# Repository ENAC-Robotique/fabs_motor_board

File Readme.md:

# Motor control board

STM32F767 based motor control board.

- control up to 3 DC motors
- 4 hardware encoder inputs.

**Holonomic drive:** Use the 3 motors, and the first 3 encoders.

**Differential drive:** Use the first 2 motors. Use the first 2 encodeurs for the motor encodeurs, and the last 2 for the odometry wheels (if applicable).

Fetch all submodules with:

`git submodule update --init --recursive`

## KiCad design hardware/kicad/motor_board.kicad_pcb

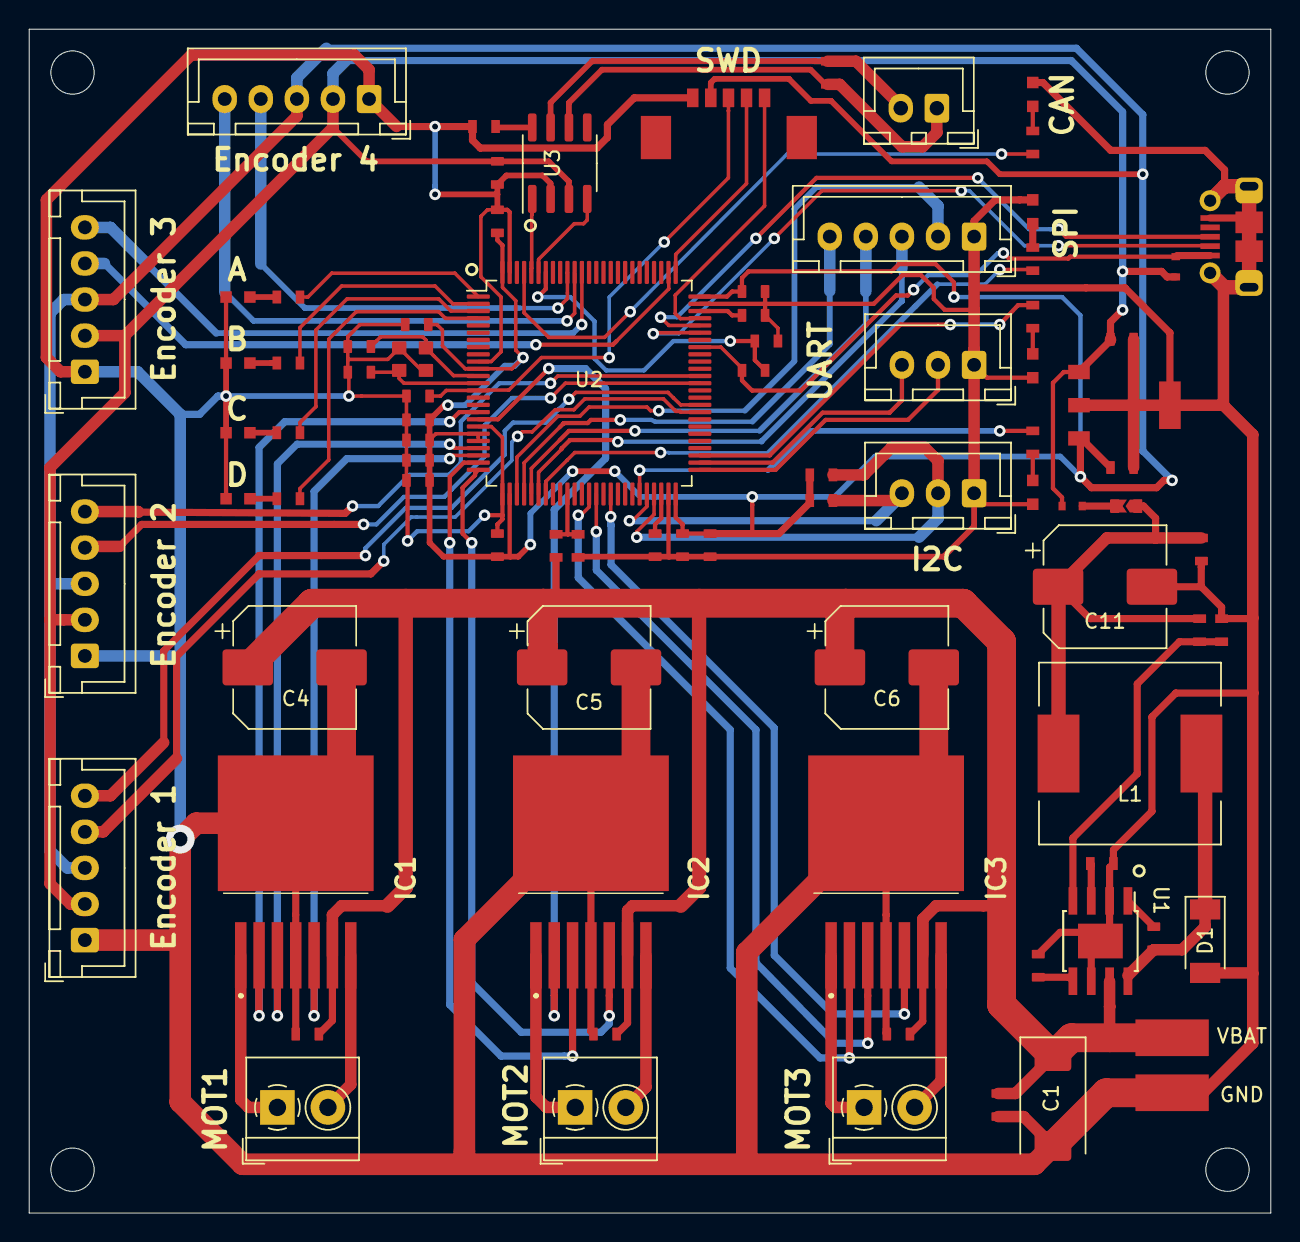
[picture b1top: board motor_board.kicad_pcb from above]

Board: 2 copper layers, 86.0 x 82.0 mm, 84 parts (0 on the bottom side), 75 nets.

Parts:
C1: 22uF; CP_EIA-7343-31_Kemet-D
C2: 6.8nF; C_0603
C3, C12, C26, C28: 1uF; C_0603
C4, C5, C6: 100uF; CP_Elec_8x10
C7, C8, C9, C17, C19, C21, C22, C23, C25, C27, C29, C30: 100nF; C_0603
C10: 10nF; C_0603
C11: 120uF; CP_Elec_8x10
C13, C14: 2.2uF; C_0603
C15, C16: 18pF; C_0603
C18: 4.7uF; C_0603
C20: 470nF; C_0603
C24: 330nF; C_0603
D1: PMEG4050ETP; D_SOD-128
D2, D3: PMEG2010EB
IC1, IC2, IC3: TLE52062GAUMA1; TLE52052GAUMA1
IC4: LM3940IMP-3.3; LM3940IMP
J1: MOT1; TerminalBlock_4Ucon_1x02_P3.50mm_Horizontal
J2: MOT2; TerminalBlock_4Ucon_1x02_P3.50mm_Horizontal
J3: MOT3; TerminalBlock_4Ucon_1x02_P3.50mm_Horizontal
J4: UART; JST_XH_B3B-XH-A_1x03_P2.50mm_Vertical
J5: I2C; JST_XH_B3B-XH-A_1x03_P2.50mm_Vertical
J6: USB_Micro-B_Rec; USB_Micro-B_Molex_105017-0001
J7: ENC2; JST_XH_B5B-XH-A_1x05_P2.50mm_Vertical
J8: ENC3; JST_XH_B5B-XH-A_1x05_P2.50mm_Vertical
J9: ENC4; JST_XH_B5B-XH-A_1x05_P2.50mm_Vertical
J10: ENC8; JST_XH_B5B-XH-A_1x05_P2.50mm_Vertical
J11: SWD; PicoBlade_53398-0571
J12: SPI; JST_XH_B5B-XH-A_1x05_P2.50mm_Vertical
J13: CAN; JST_XH_B2B-XH-A_1x02_P2.50mm_Vertical
JP1: SolderJumper_2P; SolderJumper_2P_TrianglePads_0603
L1: 8.2uH; L_Wuerth_WE-PD-Typ-LS
LED1: KP-1608CGCK
LED2, LED5, LED6, LED7, LED8: KP-1608SYC
LED3: KP-1608SURC
LED4: KP-1608SEC
P1: Power_pads
Q1: 8Z_16MHz; Crystal_8Z
R1: infΩ; R_0603
R2, R3, R4: 1.5KΩ; R_0603
R5, R10: 2.2KΩ; R_0603
R6, R7, R8, R9, R13, R14, R17, R18: 390Ω; R_0603
R11: 10KΩ; R_0603
R12: 0Ω; R_0603
R15, R16: 2.2kΩ; R_0603
R19: 120Ω; R_0603
U1: LM22673MRE-ADJ; TI_SO-PowerPAD-8
U2: STM32F767VITx; LQFP-100_14x14mm_P0.5mm
U3: MCP2551-I-SN; SOIC-8_3.9x4.9mm_P1.27mm

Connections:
+3V3: C18.2, C19.2, C21.2, C22.2, C23.2, C24.1, C25.2, C26.2, C27.2, C28.1, C29.1, IC4.3, J7.3, J8.3, J9.3, J10.3, J11.2, R15.1, R16.1, U2.11, U2.20, U2.21, U2.27, U2.50, U2.75, U2.100
+5V: C20.1, C30.2, D2.1, D3.1, IC4.1, J7.2, J8.2, J9.2, J10.2, U3.3
/ADC_POWER: R10.1, R11.1, U2.35
/CAN1_RX: U2.95, U3.4
/CAN1_TX: U2.96, U3.1
/CANH: J13.2, R19.2, U3.7
/CANL: J13.1, R19.1, U3.6
/ENC2A: J7.4, U2.77
/ENC2B: J7.5, U2.89
/ENC3A: J8.5, U2.90
/ENC3B: J8.4, U2.91
/ENC4A: J9.4, U2.59
/ENC4B: J9.5, U2.60
/ENC8A: J10.4, U2.63
/ENC8B: J10.5, U2.64
/I2C2_SCL: J5.3, R15.2, U2.46
/I2C2_SDA: J5.2, R16.2, U2.47
/LED1: R6.2, U2.1
/LED2: R7.2, U2.2
/LED3: R9.2, U2.3
/LED4: R8.2, U2.4
/LED_CAN: R14.2, U2.97
/LED_I2C: R18.2, U2.45
/LED_SPI: R17.2, U2.32
/LED_UART: R13.2, U2.53
/NRST: C17.2, J11.3, U2.14
/PWM1A: IC1.3, U2.22
/PWM1B: IC1.5, U2.23
/PWM2A: IC2.3, U2.24
/PWM2B: IC2.5, U2.25
/PWM3A: IC3.3, U2.39
/PWM3B: IC3.5, U2.41
/SPI1_MISO: J12.4, U2.30
/SPI1_MOSI: J12.3, U2.31
/SPI1_NSS: J12.2, U2.28
/SPI1_SCK: J12.5, U2.29
/SWDCLK: J11.4, U2.76
/SWDIO: J11.5, U2.72
/TLE_EF_1: IC1.2, U2.17
/TLE_EF_2: IC2.2, U2.18
/TLE_EF_3: IC3.2, U2.38
/UART5_RX: J4.2, U2.51
/UART5_TX: J4.3, U2.52
/USB_DM: J6.2, U2.70
/USB_DP: J6.3, U2.71
/USB_VBUS: D3.2, J6.1, R4.2, U2.68
GND: C1.2, C2.1, C3.1, C4.2, C5.2, C6.2, C7.1, C8.1, C9.1, C11.2, C12.1, C13.2, C14.2, C15.1, C16.2, C17.1, C18.1, C19.1, C20.2, C21.1, C22.1, C23.1, C24.2, C25.1, C26.1, C27.1, C28.2, C29.2, C30.1, D1.2, IC1.4, IC1.8, IC2.4, IC2.8, IC3.4, IC3.8, IC4.2, IC4.4, J4.1, J5.1, J6.5, J6.6, J7.1, J8.1, J9.1, J10.1, J11.1, J12.1, LED1.1, LED2.1, LED3.1, LED4.1, LED5.1, LED6.1, LED7.1, LED8.1, P1.1, Q1.2, Q1.4, R1.1, R3.2, R5.1, R10.2, R12.2, U1.2, U1.6, U1.9, U2.10, U2.19, U2.26, U2.49, U2.74, U2.99, U3.2
unnamed: C3.2, U1.5
unnamed: C10.1, U1.1
unnamed: C10.2, D1.1, L1.1, U1.8
unnamed: C11.1, C12.2, JP1.1, L1.2, R2.1
unnamed: C13.1, U2.48
unnamed: C14.1, U2.73
unnamed: C15.2, Q1.1, U2.12
unnamed: C16.1, Q1.3, U2.13
unnamed: D2.2, JP1.2
unnamed: IC1.1, J1.1
unnamed: IC1.7, J1.2
unnamed: IC2.1, J2.1
unnamed: IC2.7, J2.2
unnamed: IC3.1, J3.1
unnamed: IC3.7, J3.2
unnamed: LED1.2, R6.1
unnamed: LED2.2, R7.1
unnamed: LED3.2, R8.1
unnamed: LED4.2, R9.1
unnamed: LED5.2, R13.1
unnamed: LED6.2, R14.1
unnamed: LED7.2, R17.1
unnamed: LED8.2, R18.1
unnamed: R1.2, U1.3
unnamed: R2.2, R3.1, U1.4
unnamed: R4.1, R5.2, U2.94
unnamed: R12.1, U3.8
VBAT: C1.1, C2.2, C4.1, C5.1, C6.1, C7.2, C8.2, C9.2, IC1.6, IC2.6, IC3.6, P1.2, R11.2, U1.7

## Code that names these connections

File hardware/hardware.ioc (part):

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Mcu.Name=STM32F767VITx
Mcu.Package=LQFP100
Mcu.UserName=STM32F767VITx
PA0/WKUP.Signal=S_TIM5_CH1
PA1.Signal=S_TIM5_CH2
PA11.Mode=Device_Only
PA11.Signal=USB_OTG_FS_DM
PA12.Mode=Device_Only
PA12.Signal=USB_OTG_FS_DP
PA13.Mode=Serial_Wire
PA13.Signal=SYS_JTMS-SWDIO
PA14.Mode=Serial_Wire
PA14.Signal=SYS_JTCK-SWCLK
PA15.Signal=S_TIM2_CH1_ETR
PA2.Signal=S_TIM5_CH3
PA3.Signal=S_TIM5_CH4
PA4.Mode=NSS_Signal_Hard_Input
PA4.Signal=SPI1_NSS
PA5.Mode=Full_Duplex_Slave
PA5.Signal=SPI1_SCK
PA6.Mode=Full_Duplex_Slave
PA6.Signal=SPI1_MISO
PA7.Mode=Full_Duplex_Slave
PA7.Signal=SPI1_MOSI
PA9.Mode=Activate_VBUS
PA9.Signal=USB_OTG_FS_VBUS
PB1.Signal=ADCx_IN9
PB10.Mode=I2C
PB10.Signal=I2C2_SCL
PB11.Mode=I2C
PB11.Signal=I2C2_SDA
PB12.Mode=Asynchronous
PB12.Signal=UART5_RX
PB13.Mode=Asynchronous
PB13.Signal=UART5_TX
PB14.Signal=GPIO_Output
PB3.Signal=S_TIM2_CH2
PB4.Signal=S_TIM3_CH1
PB5.Signal=S_TIM3_CH2
PB8.Mode=Master
PB8.Signal=CAN1_RX
PB9.Mode=Master
PB9.Signal=CAN1_TX
PC13.Signal=GPIO_Input
PC14/OSC32_IN.Signal=GPIO_Input
PC15/OSC32_OUT.Signal=GPIO_Input
PC2.Signal=GPIO_Input
PC3.Signal=GPIO_Input
PC4.Signal=GPIO_Output
PC6.Signal=S_TIM8_CH1
PC7.Signal=S_TIM8_CH2
PD12.Signal=S_TIM4_CH1
PD13.Signal=S_TIM4_CH2
PE0.Signal=GPIO_Output
PE11.Signal=S_TIM1_CH2
PE12.Signal=GPIO_Input
PE13.Signal=S_TIM1_CH3
PE14.Signal=S_TIM1_CH4
PE15.Signal=GPIO_Output
PE2.Signal=GPIO_Output
PE3.Signal=GPIO_Output
PE4.Signal=GPIO_Output
PE5.Signal=GPIO_Output
PE6.Signal=GPIO_Input
PE8.Signal=GPIO_Input
PE9.Signal=S_TIM1_CH1
PH0/OSC_IN.Mode=HSE-External-Oscillator
PH0/OSC_IN.Signal=RCC_OSC_IN
PH1/OSC_OUT.Mode=HSE-External-Oscillator
PH1/OSC_OUT.Signal=RCC_OSC_OUT
RCC.HSE_VALUE=16000000
board=custom

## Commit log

2019-10-31 Adds readme
2019-11-18 Update GRZ libs submodule.
2019-11-18 Hopefully finish schematic.
2019-11-18 Begins PCB design.
2019-11-18 Adds diodes to power board via usb.
2019-11-18 Finish PCBV0.1
2019-11-18 Update libs FBO.
2019-11-18 Edit for Stencil
2019-12-16 minor changes
2019-12-16 Back to original size (no stencil)
2020-01-25 Adds STM32 docs.
2020-01-25 Adds part of CMSIS DSP.
2020-01-25 Serial Communication.
2020-01-25 Odometry for diff drive - no coding wheels.
2020-01-25 Begins firmware.
2020-01-25 Big mess, up to beginning of speed control.
2020-01-25 Use USB Serial.
2020-01-25 Adds power voltage check.
2020-01-26 Fix submodule URL.
2021-11-08 Use protobuf, remove old Ducklink.
2021-11-08 Update submodules
2021-11-08 Add .gitignore.
2021-11-08 Move code to subdirectory.
2021-11-08 Set motor command range to [-100, 100]
2021-11-08 Move power check in its own file.
2021-11-08 Add message.
2021-11-08 Add mailboxes to exchange messages.
2021-11-08 Test parse message.
2021-11-08 Add main back.
2021-11-09 Convert motor.c to cpp and use templates.
2021-11-09 vscode config.
2021-11-09 Add HolonomicControl.
2021-11-09 continue moving to C++
2021-11-09 Odometry and stuff.
2021-11-10 Improve receiver, and send data to plotjuggler.
2021-11-17 com params
2021-11-17 set odom params
2021-11-17 Use and tune coding wheels.
2021-11-18 Fix asserv
2021-11-18 Increase stack size.
2021-11-18 Gig bad mess
2021-11-18 Add speed command safety time.
2021-11-19 Fix minor bugs
2021-11-19 comment printfs
2021-11-20 PID filter input and saturate integrator.
2021-11-20 Update messages.
2021-11-21 [com] receive payload all at once if possible.
2021-12-13 Allow setting position.
2021-12-14 Add slip detection.
2022-03-23 change motors directions.
2022-04-13 Start better organisation.
2022-04-14 Reduce global variables.
2022-04-14 move more code.
2022-04-15 [Diff] Increase accel max.
2022-04-20 Begin Holo control.
2022-04-20 Remove CMSIS ARM math.
2022-04-20 Make holonomic odometry.
2022-04-20 Add some debug stuff
2022-04-21 [OdometryHolo] Speed in robot frame.
2022-04-21 Fix index error.
2022-04-21 [HolonomicControl] Simple P control.
2022-04-25 [HolonomicControl] Add integral term, and feedforward.
2022-04-25 small cleaning
2022-04-26 [Diff] Fix time error.
2022-04-28 Update Embedded proto.
2022-04-29 Initialize console before use of chprintf.
2022-04-29 ChibiOS, re-enable debugs ands tick mode.
2022-05-16 Add image to readme.
2022-05-19 Magic number to compensate for different motor.
2022-05-19 Tune Holo odometry
2022-05-19 do not report motors speed
2023-11-13 nimportequoi
2023-11-13 cppzation
2023-11-14 add update filters method
2023-11-15 working !
2023-11-15 move filters
2023-11-15 organizing
2023-11-15 python receiver.
2023-11-15 Update Embedded Proto and protoduck.
2023-11-15 Add mot_pos_cons to telemetry.
2023-11-15 report period
2023-11-15 prevent error.
2023-11-17 Start guidance.
2023-11-17 cleanup
2023-11-17 Fix setpoint error
2023-11-20 refactor
